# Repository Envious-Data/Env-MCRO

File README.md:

# Env-MCRO
 A Raspberry Pi Pico powered Macro board, like a Streamdeck but cheaper and simpler.

(btw this image is a bit outdated, some of the silkscreen has changed but its physically the same)

### What This?
This is another another mechanical keyboard type thing, this is a small 12 key macro board intended to be used for F13 to F24 but you can do whatever.
I do feel like the rpi pico is a bit overkill for this use, a tiny2040 will probably fit better, Ill have to see if someone has made kidcad bits for that if not Ill probably have to make them my self or whatever.

### Parts List
* 1x Raspberry Pi Pico
* 12x Keyboard Switches
* 12x 1N4148 Diodes (through hole)
* 12x Keycaps
* 1x Rotary Encoder (optional)
* 12X SK6812 Mini-e LEDs (optional)
* Macro Board PCB
- (The board dimentions are: 109.6mm x 69.7mm)

### Quick setup guide
* Connect the Raspberry pi pico to your PC holding the Bootsel button
  * a USB Drive should show up called RP2-BOOT
* Download [This](blob:https://github.com/d1d8b8da-7e8d-4b2f-9aaf-276d6753a1cd) File and copy it to the drive called RP2-BOOT

the board should reboot and startup with the default keymap, you are good to use it however you wish but if you wish to re-map the board you can look at the QMK code and modify it as you see fit.

By default the macro board is mapped with keys F13 to F24 but you can go [Here](https://github.com/KMKfw/kmk_firmware/blob/master/docs/en/keycodes.md) and look at what keys you can re-map with.

not all software supports the F13 to F24 keys but a couple of examples that do are OBS and BeamNG.Drive

### QMK
Ive built QMK for these boards, if you want to remap it be sure to use the VIA version of the MCRO firmware, download the respective via JSON from the folder and sideload it in via.
https://github.com/Envious-Data/EnvKB-QMK/tree/main/_PREBUILTFIRMWARES

### extra bits!
User TonyPJ on Thingiverse has made a small 3d printable stand: https://www.thingiverse.com/thing:4896875

Project was Selected for Booster Conf as part of a Mechanical Keyboards Talk, a 3d printable case was made and can be found here: https://github.com/vidarw/booster-2025-macroboard

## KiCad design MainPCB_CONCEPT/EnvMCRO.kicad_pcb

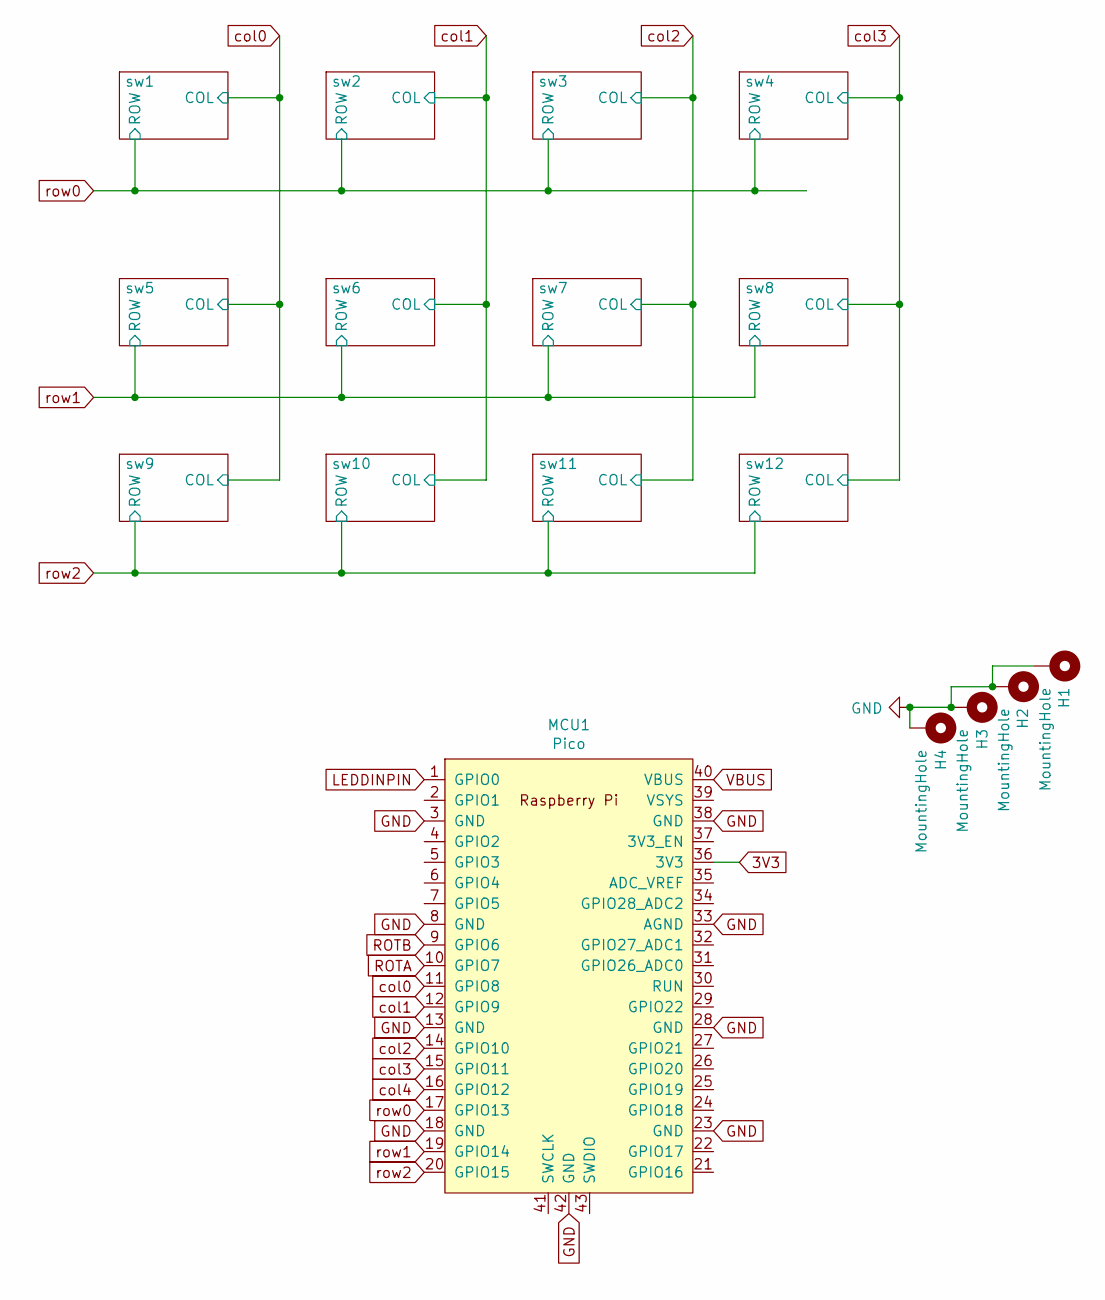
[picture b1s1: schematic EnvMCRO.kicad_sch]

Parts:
H1, H2, H3, H4: MountingHole; MountingHole_2.2mm_M2_Pad
MCU1: Pico; RPi_Pico_SMD_TH

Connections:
3V3: MCU1.36 (3V3); also elsewhere on the board
GND: H1.1, H2.1, H3.1, H4.1, MCU1.3 (GND), MCU1.8 (GND), MCU1.13 (GND), MCU1.18 (GND), MCU1.23 (GND), MCU1.28 (GND), MCU1.33 (AGND), MCU1.38 (GND), MCU1.42 (GND); also elsewhere on the board
LEDDINPIN: MCU1.1 (GPIO0)
ROTA: MCU1.10 (GPIO7)
ROTB: MCU1.9 (GPIO6)
VBUS: MCU1.40 (VBUS)
col0: MCU1.11 (GPIO8); also elsewhere on the board
col1: MCU1.12 (GPIO9); also elsewhere on the board
col2: MCU1.14 (GPIO10); also elsewhere on the board
col3: MCU1.15 (GPIO11); also elsewhere on the board
col4: MCU1.16 (GPIO12)
row0: MCU1.17 (GPIO13); also elsewhere on the board
row1: MCU1.19 (GPIO14); also elsewhere on the board
row2: MCU1.20 (GPIO15); also elsewhere on the board

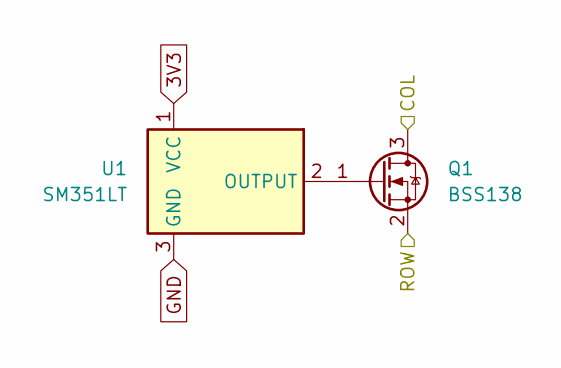
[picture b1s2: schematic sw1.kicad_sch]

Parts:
Q1: BSS138; SOT-23
U1: SM351LT; SOT-23

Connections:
3V3: U1.1 (VCC); also elsewhere on the board
GND: U1.3 (GND); also elsewhere on the board
unnamed: Q1.1 (G), U1.2 (OUTPUT)
col0: Q1.3 (D); also elsewhere on the board
row0: Q1.2 (S); also elsewhere on the board

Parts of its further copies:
Q2, Q3, Q4, Q5, Q6, Q7, Q8, Q9, Q10, Q11, Q12: BSS138; SOT-23
U2, U3, U4, U5, U6, U7, U8, U9, U10, U11, U12: SM351LT; SOT-23

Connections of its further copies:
3V3: U2.1 (VCC), U3.1 (VCC), U4.1 (VCC), U5.1 (VCC), U6.1 (VCC), U7.1 (VCC), U8.1 (VCC), U9.1 (VCC), U10.1 (VCC), U11.1 (VCC), U12.1 (VCC); also elsewhere on the board
GND: U2.3 (GND), U3.3 (GND), U4.3 (GND), U5.3 (GND), U6.3 (GND), U7.3 (GND), U8.3 (GND), U9.3 (GND), U10.3 (GND), U11.3 (GND), U12.3 (GND); also elsewhere on the board
unnamed: Q2.1 (G), U2.2 (OUTPUT)
unnamed: Q3.1 (G), U3.2 (OUTPUT)
unnamed: Q4.1 (G), U4.2 (OUTPUT)
unnamed: Q5.1 (G), U5.2 (OUTPUT)
unnamed: Q6.1 (G), U6.2 (OUTPUT)
unnamed: Q7.1 (G), U7.2 (OUTPUT)
unnamed: Q8.1 (G), U8.2 (OUTPUT)
unnamed: Q9.1 (G), U9.2 (OUTPUT)
unnamed: Q10.1 (G), U10.2 (OUTPUT)
unnamed: Q11.1 (G), U11.2 (OUTPUT)
unnamed: Q12.1 (G), U12.2 (OUTPUT)
col0: Q5.3 (D), Q9.3 (D); also elsewhere on the board
col1: Q2.3 (D), Q6.3 (D), Q10.3 (D); also elsewhere on the board
col2: Q3.3 (D), Q7.3 (D), Q11.3 (D); also elsewhere on the board
col3: Q4.3 (D), Q8.3 (D), Q12.3 (D); also elsewhere on the board
row0: Q2.2 (S), Q3.2 (S), Q4.2 (S); also elsewhere on the board
row1: Q5.2 (S), Q6.2 (S), Q7.2 (S), Q8.2 (S); also elsewhere on the board
row2: Q9.2 (S), Q10.2 (S), Q11.2 (S), Q12.2 (S); also elsewhere on the board

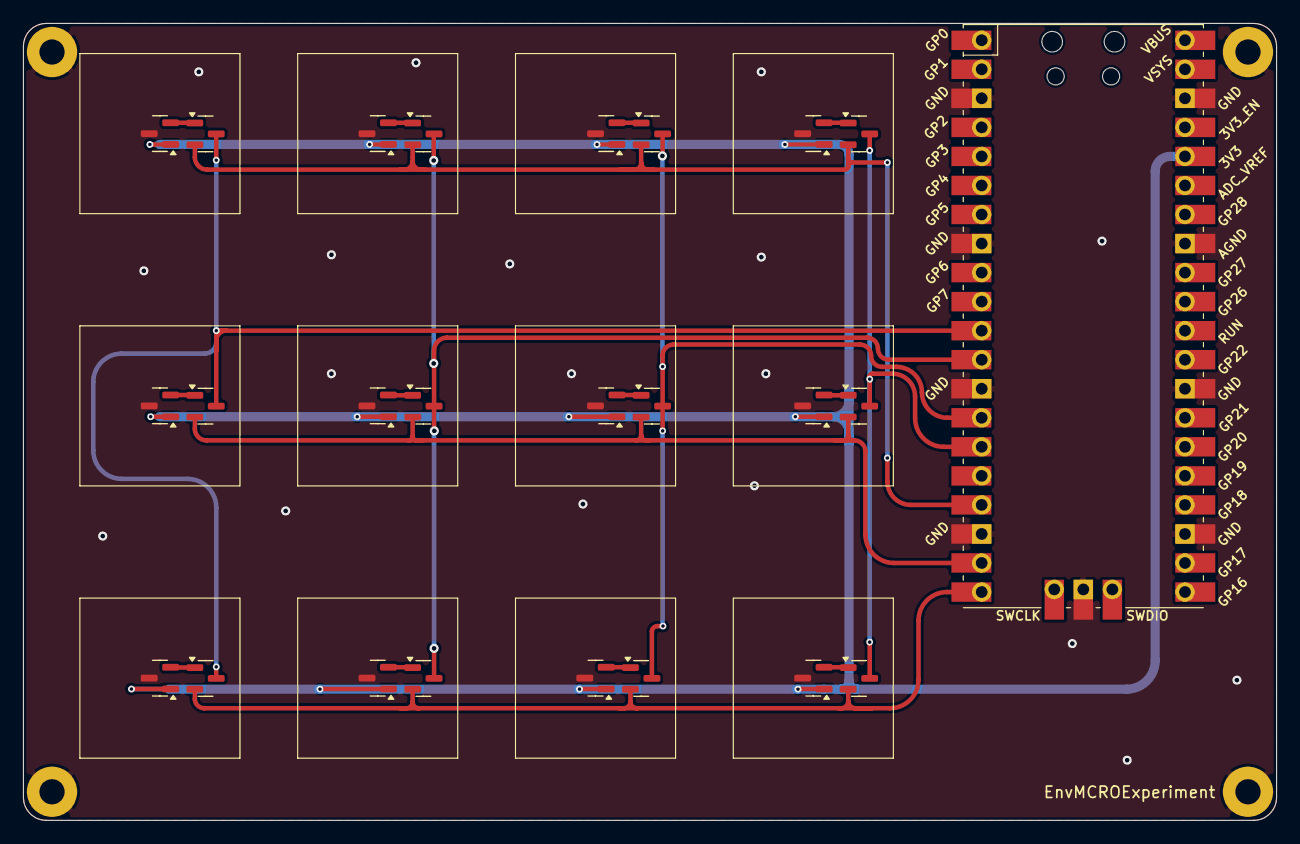
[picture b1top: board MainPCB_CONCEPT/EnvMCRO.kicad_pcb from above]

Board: 2 copper layers, 109.6 x 69.7 mm, 29 parts (0 on the bottom side), 21 nets.

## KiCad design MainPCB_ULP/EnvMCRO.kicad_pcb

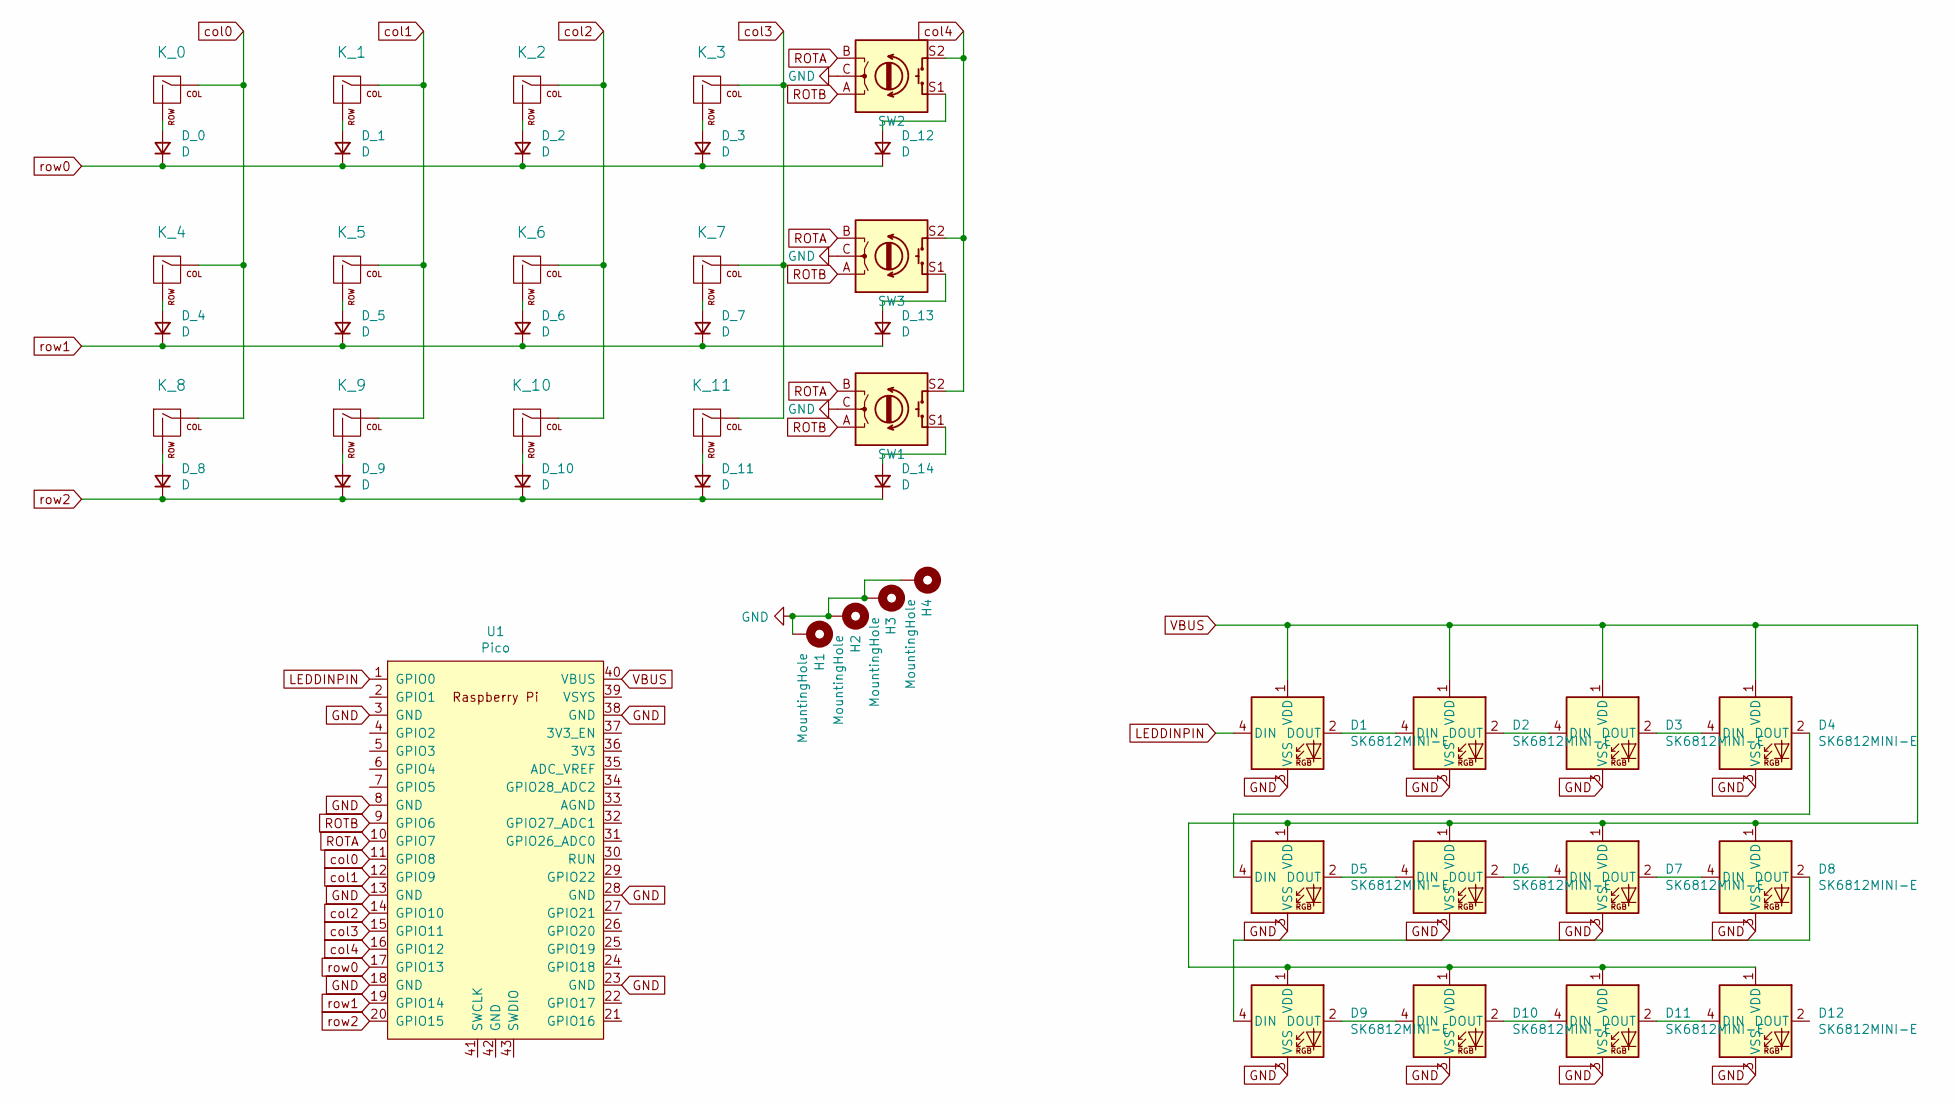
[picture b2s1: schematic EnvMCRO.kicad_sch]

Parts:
D1, D2, D3, D4, D5, D6, D7, D8, D9, D10, D11, D12: SK6812MINI-E; MX_SK6812MINI-E_REV
D_0, D_1, D_2, D_3, D_4, D_5, D_6, D_7, D_8, D_9, D_10, D_11, D_12, D_13, D_14: D; D_DO-35_SOD27_P7.62mm_Horizontal
H1, H2, H3, H4: MountingHole; MountingHole_2.2mm_M2_Pad
K_0, K_1, K_2, K_3, K_4, K_5, K_6, K_7, K_8, K_9, K_10, K_11: KEYSW; Cherry_MX_ULP
SW1, SW2, SW3: Rotary_Encoder_Switch; RotaryEncoder_Alps_EC12E-Switch_Vertical_H20mm
U1: Pico; RPi_Pico_SMD_TH

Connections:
LEDDINPIN: D1.4 (DIN), U1.1 (GPIO0)
unnamed: D1.2 (DOUT), D2.4 (DIN)
unnamed: D2.2 (DOUT), D3.4 (DIN)
unnamed: D3.2 (DOUT), D4.4 (DIN)
unnamed: D4.2 (DOUT), D5.4 (DIN)
unnamed: D5.2 (DOUT), D6.4 (DIN)
unnamed: D6.2 (DOUT), D7.4 (DIN)
unnamed: D7.2 (DOUT), D8.4 (DIN)
unnamed: D8.2 (DOUT), D9.4 (DIN)
unnamed: D10.2 (DOUT), D11.4 (DIN)
unnamed: D9.2 (DOUT), D10.4 (DIN)
unnamed: D11.2 (DOUT), D12.4 (DIN)
unnamed: D_0.2 (A), K_0.2 (ROW)
unnamed: D_1.2 (A), K_1.2 (ROW)
unnamed: D_2.2 (A), K_2.2 (ROW)
unnamed: D_3.2 (A), K_3.2 (ROW)
unnamed: D_4.2 (A), K_4.2 (ROW)
unnamed: D_5.2 (A), K_5.2 (ROW)
unnamed: D_6.2 (A), K_6.2 (ROW)
unnamed: D_7.2 (A), K_7.2 (ROW)
unnamed: D_8.2 (A), K_8.2 (ROW)
unnamed: D_9.2 (A), K_9.2 (ROW)
unnamed: D_10.2 (A), K_10.2 (ROW)
unnamed: D_11.2 (A), K_11.2 (ROW)
unnamed: D_12.2 (A), SW2.S1
unnamed: D_13.2 (A), SW3.S1
unnamed: D_14.2 (A), SW1.S1
ROTA: SW1.B, SW2.B, SW3.B, U1.10 (GPIO7)
ROTB: SW1.A, SW2.A, SW3.A, U1.9 (GPIO6)
VBUS: D1.1 (VDD), D2.1 (VDD), D3.1 (VDD), D4.1 (VDD), D5.1 (VDD), D6.1 (VDD), D7.1 (VDD), D8.1 (VDD), D9.1 (VDD), D10.1 (VDD), D11.1 (VDD), D12.1 (VDD), U1.40 (VBUS)
col0: K_0.1 (COL), K_4.1 (COL), K_8.1 (COL), U1.11 (GPIO8)
col1: K_1.1 (COL), K_5.1 (COL), K_9.1 (COL), U1.12 (GPIO9)
col2: K_2.1 (COL), K_6.1 (COL), K_10.1 (COL), U1.14 (GPIO10)
col3: K_3.1 (COL), K_7.1 (COL), K_11.1 (COL), U1.15 (GPIO11)
col4: SW1.S2, SW2.S2, SW3.S2, U1.16 (GPIO12)
row0: D_0.1 (K), D_1.1 (K), D_2.1 (K), D_3.1 (K), D_12.1 (K), U1.17 (GPIO13)
row1: D_4.1 (K), D_5.1 (K), D_6.1 (K), D_7.1 (K), D_13.1 (K), U1.19 (GPIO14)
row2: D_8.1 (K), D_9.1 (K), D_10.1 (K), D_11.1 (K), D_14.1 (K), U1.20 (GPIO15)

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
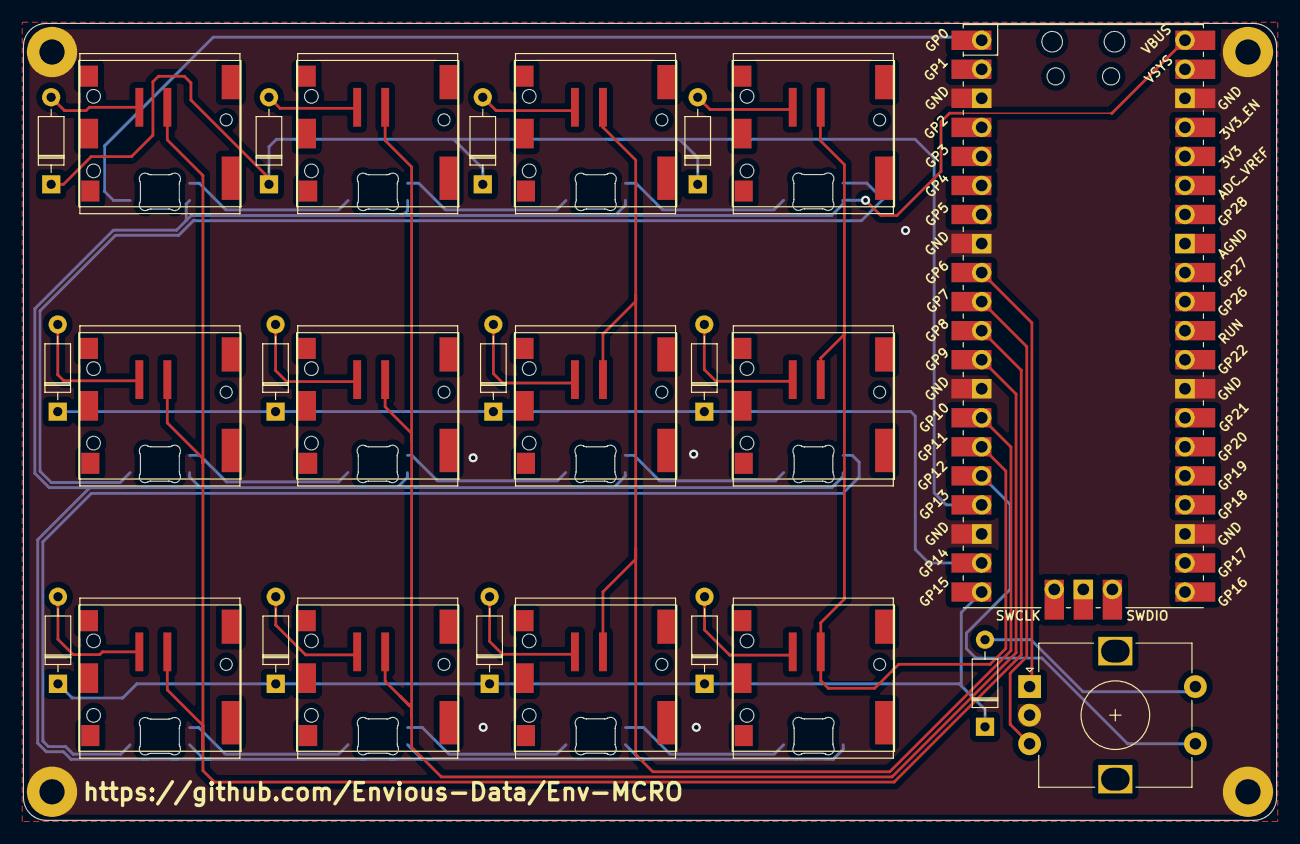
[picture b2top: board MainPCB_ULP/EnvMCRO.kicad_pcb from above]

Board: 2 copper layers, 109.6 x 69.7 mm, 45 parts (0 on the bottom side), 37 nets.

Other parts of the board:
kibuzzard-63CB16AC: G***; kibuzzard-63CB16AC
kibuzzard-63CB16FA: G***; kibuzzard-63CB16FA

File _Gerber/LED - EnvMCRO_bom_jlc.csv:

"Comment","Designator","Footprint","LCSC Part #"
"SK6812","D1,D2,D3,D4,D5,D6,D7,D8,D9,D10,D11,D12","LED_SK6812MINI_PLCC4_3.5x3.5mm_P1.75mm","no_part_number"
"D","D_11,D_10,D_9,D_8,D_7,D_6,D_5,D_4,D_3,D_2,D_1,D_0","D_DO-35_SOD27_P7.62mm_Horizontal","no_part_number"
"MountingHole","H1,H2,H3,H4","MountingHole_2.2mm_M2","no_part_number"
"KEYSW","K_11,K_10,K_9,K_8,K_7,K_6,K_5,K_4,K_3,K_2,K_1,K_0","MXOnly-1U-NoLED","no_part_number"
"Pico","U1","RPi_Pico_SMD_TH","no_part_number"

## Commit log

2021-04-11 Added Files
2021-04-11 small woopsies in the readme
2021-04-11 Added Image
2021-04-11 Removed unused pads, Added modified footprint of rpi pico
2021-04-11 Added lines for plate and backing.
2021-04-11 Added some Gerber bits and SVGs for laser cutting
2021-04-17 Some Mechanical CAD Work.
2021-04-21 Updated Laser Cut SVGs
2021-04-30 Correct Laser cut DXF
    This change needs to be un-done every time you generate a gerber
2021-05-01 Uploaded a Generic Keymap example
2021-05-02 Fixed the error in the silkscreen
    "http://https://" idk how I missed this
2021-05-02 Updated Gerber bits with new graphics design
    and also correct format!
2021-05-03 Updated graphics design on board
    added the github URL back but now its shiny!
2021-05-03 Additional silkscreen design
2021-05-08 Added a gerber for plain pcb w/ no graphics
2021-05-26 Initial Requirement for simpler guide
2021-05-26 Simplified the guide
2021-05-26 Cleaned up repo, created backing PCB.
2021-05-27 Added Mechboards logo for later use
2021-05-27 Added logo to back plate
2021-05-31 Renamed Gerber files so they are easier to work with in large orders
2021-06-04 Added Pads/traces for 3535 SK6812 or WS2812B
2021-06-05 smol aesthetic tweak
2021-06-06 better RGB implementation using SK6812 MINI E footprints to be installed reverse on the back of the PCB + generated gerber
2021-08-25 testing new graphic for the board.
2021-09-04 organized stuff a bit, added rotary encoder, added pro micro version with 2 rotary encoders.
2021-09-05 updated macro boards to have padded mount holes and github url
2021-09-05 swapped EC11 for EC12 because cheaper, might swap again to what ever people get a hold of the easiest.
2021-09-13 created a version with both a pro micro and a pico footprint
2021-10-19 updated keymap to support the latest KMK
2021-11-20 small fix for the CPL
2021-11-22 fixed pads and generated updated gerber
2021-11-26 updated firmware to latest version
2022-01-11 exported model to design a case around (tempoary)
2022-03-24 some updates and got rid of other versions, plan to make a XL version in the future that will stay.
2023-01-20 renamed main version to make more sense in the future and created a MX ULP version
2023-01-20 update gitignore
2024-11-21 update readme so its no longer hugely outdated.
2025-02-26 made experimental magnet wand board.
